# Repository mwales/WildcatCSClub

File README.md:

# WildcatCSClub

Repository for artifacts for helping the WildCat CS Club (formerly Cyber
Security Club), now Computer Science Club.

[Prior year challenges (with sample writeups)](past_challenges/year_2022_2023) are available. This is only a subset
of the 50 or so challenges the we worked on over the year.

[Slides from this year and prior years](slides/readme.md) are also available.

# Links to local in-person competitions

* [Lockheed Martin Code Quest Information](https://www.lockheedmartin.com/en-us/who-we-are/communities/codequest.html)
* [2023 Code Quest Pictures](https://lockheedmartin.smugmug.com/Code-Quest/Code-Quest-2023/FL-Orlando/)
* [Lockheed Martin Cyber Quest Information](https://www.lockheedmartin.com/en-us/who-we-are/communities/cyber-quest.html)
* [2023 Cyber Quest Pictures](https://lockheedmartin.smugmug.com/CYBERQUEST/CYBERQUEST-2023/Orlando-FL/)
* [2024 Code Quest Pictures](https://lockheedmartin.smugmug.com/Code-Quest/2024-Code-Quest/FL-Orlando)
* [2024 Cyber Quest Pictures](https://lockheedmartin.smugmug.com/CYBERQUEST/Cyber-Quest-2024/FL-Orlando)

## Other possible in-person competition option for 2023-2024

* [UCF High School Programming Tournament](https://hspt.ucfprogrammingteam.org/index.php/hspt/this-year-s-tournament)

# Online Events

* [Pico CTF](https://picoctf.org/) - Carnegie Mellon University

* [TJ CTF](https://tjctf.org) - Thomas Jefferson High School for Sciene and Technology (#5 high school in the country per Forbes)

# Why CTF?

# Sponsors and Support

Generous support was given to the club from the following organizations.  The kids didn't have to pay for anything out
of pocket.  Sponsors provided loaner laptops, T-shirts for competitions, and [Binary Ninja](https://binary.ninja) 
discounts and licenses, along with their time.

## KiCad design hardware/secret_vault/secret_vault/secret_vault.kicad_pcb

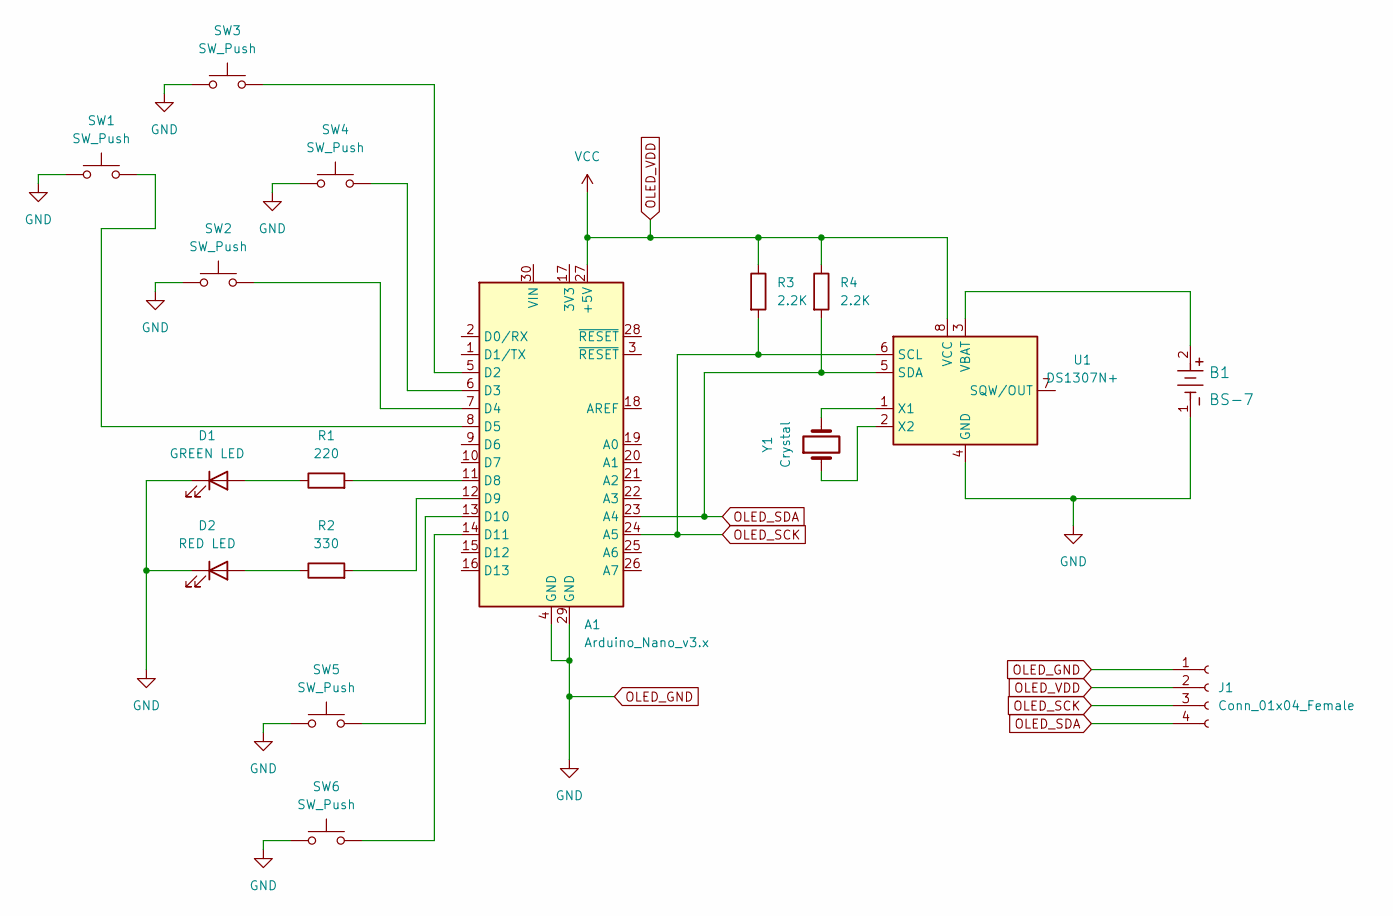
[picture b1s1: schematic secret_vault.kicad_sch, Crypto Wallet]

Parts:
A1: Arduino_Nano_v3.x; Arduino_Nano
B1: BS-7; BS-7_MPD
D1: GREEN LED; LED_D5.0mm
D2: RED LED; LED_D5.0mm
J1: Conn_01x04_Female; PinSocket_1x04_P2.54mm_Vertical
R1: 220; R_Axial_DIN0309_L9.0mm_D3.2mm_P12.70mm_Horizontal
R2: 330; R_Axial_DIN0309_L9.0mm_D3.2mm_P12.70mm_Horizontal
R3, R4: 2.2K; R_Axial_DIN0309_L9.0mm_D3.2mm_P12.70mm_Horizontal
SW1, SW2, SW3, SW4, SW5, SW6: SW_Push; SW_TH_Tactile_Omron_B3F-10xx_stackedpninums
U1: DS1307N+; DIP-8_W7.62mm
Y1: Crystal; Crystal_C26-LF_D2.1mm_L6.5mm_Horizontal

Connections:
unnamed: A1.5 (D2), SW3.2
unnamed: A1.6 (D3), SW4.2
unnamed: A1.7 (D4), SW2.2
unnamed: A1.8 (D5), SW1.2
unnamed: A1.11 (D8), R1.2
unnamed: A1.12 (D9), R2.2
unnamed: A1.13 (D10), SW5.2
unnamed: A1.14 (D11), SW6.2
unnamed: B1.2, U1.3 (VBAT)
unnamed: D1.2 (A), R1.1
unnamed: D2.2 (A), R2.1
unnamed: U1.1 (X1), Y1.2
unnamed: U1.2 (X2), Y1.1
OLED_GND: A1.4 (GND), A1.29 (GND), B1.1, D1.1 (K), D2.1 (K), J1.1, SW1.1, SW2.1, SW3.1, SW4.1, SW5.1, SW6.1, U1.4 (GND)
OLED_SCK: A1.24 (A5), J1.3, R3.2, U1.6 (SCL)
OLED_SDA: A1.23 (A4), J1.4, R4.2, U1.5 (SDA)
OLED_VDD: A1.27 (+5V), J1.2, R3.1, R4.1, U1.8 (VCC)

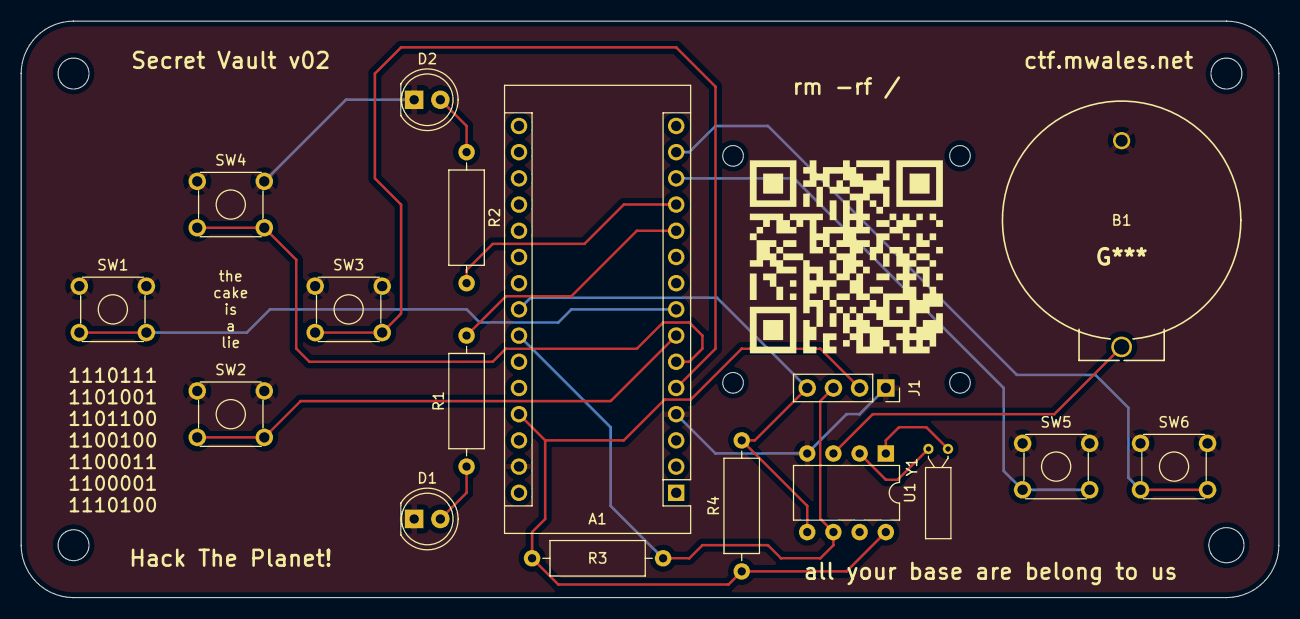
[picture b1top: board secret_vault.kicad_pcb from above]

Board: 2 copper layers, 121.9 x 55.9 mm, 17 parts (0 on the bottom side), 17 nets.

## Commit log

2021-10-08 First CPXI writeup
2021-10-08 Trying to improve formatting of my writeup
2021-10-21 Cheatsheet in progress
2021-10-22 More updates to Linux notes
2021-10-22 Added a few more commands
2022-09-22 Old cyberpatriot writeup stuff I never commited
2022-09-22 Moving cyberpatriot stuff into own folder
2022-09-22 Updating linux cheatsheet for CTF students
2022-09-22 Updating readme with new club name
2022-09-23 Fixed Searching/Investigation and minor edits
2022-09-23 Cheatsheet updates
2022-09-23 Made printable PDF
2022-09-23 week 1 slides
2022-10-07 Udpated slides
2022-10-14 Added Hacker Stories presentation
2022-10-28 Added level 4 slides
2023-01-13 slides
2023-01-13 Fix formatting on link
2023-02-03 Finished Level 5 slides - More C
2023-02-24 Cyber Quest Info
2023-04-14 Level 6 slides - Code Quest prep
2023-04-14 Add Code Quest parent meeting slides
2023-04-28 Added slides for finale
2023-08-23 Adding 2 past year challenges
2023-08-23 Adding some links and sponsor info to main page
2023-08-23 Updating some markdown
2023-08-23 More typos fixed
2023-08-24 Added 3 more sample challenges
2023-08-24 Added another challenge
2023-08-24 Fixing null cipher writeup and sample problems
2023-08-24 Mixed up my null ciphers
2023-08-24 Added second null cipher challenge
2023-08-24 Updated main README with links to prior challneges
2023-09-01 New slides
2023-09-05 Cool presentation on how to promote hacking skills in students
2023-09-08 Added new slides for this week
2023-09-22 Simple TCP and UDP examples
2023-09-22 TCP and UDP slides
2023-09-29 Created schematic for secret vault hardware device
2023-10-06 Added octal dump and slides for this week
2023-10-13 Adding Programming Tips slides
2023-10-14 Updated PCB board and sent it to OSH park for fab
2023-10-20 Career day slides uploaded
2023-10-27 Into to C 2023 presentation
2023-11-03 Added notes
2023-11-08 Adding screencaps from kicad of the schematic and PCB
2023-11-08 Many fixes to the v0.2 secret vault board
    - Added pullup resistor for I2C lines
    - All of the switch footprints were wrong
    - RTC Vcc tied to 5V instead of Vin
    - Added QR code to silkscreen
    - Made the resistors a larger part
    - Enlarged many of the fonts
2023-11-08 Didn't have PCB saved
2023-11-08 Updated OSH Park image for secret vault 0.2
2023-11-17 Adding level 7
2024-01-26 Command Injection Vulnerability
2024-01-26 Forgot to save before last commit
2024-01-26 Updating notes for students. Bugs this week.
2024-01-26 Stack overflow example
2024-01-26 Forgot the code for the stack int array
2024-01-26 Added comment to example code on how to compile
2024-02-02 Slides updated
2024-02-09 Added new slides about CyberGen Camp
2024-02-16 Adding slides on Hashing
2024-02-23 New slides created, added link
2024-03-01 Storing secrets slides
2024-03-22 Slides about Conway's Life and File Permissions
2024-03-22 Made some updates to Game of Life.pdf
2024-04-03 Adding some partial writeups as the year winds down
2024-04-03 Fixing broken links in writeups and what not
2024-04-04 Password Checker partial writeup
2024-04-04 Renamed directory for password checker writeup
2024-04-04 Fixed typo in writeup link
2024-04-04 Still can't splel
2024-04-26 Added 2024 contest picture link
2024-04-26 Added SCM and git slides
2024-05-03 Last presentation of the year
2024-05-04 End of year wrap-up
2024-05-04 Forgot to save the readme
2024-05-04 Adding top 10 chart
